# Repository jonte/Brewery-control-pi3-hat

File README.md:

This is a KiCad schematic of the outlines of a Raspberry Pi 2/3/4 HAT. The
schematic conforms to the official [HAT mechanical
specification](https://github.com/raspberrypi/hats/blob/master/hat-board-mechanical.pdf).

The intended use of this schematic is as a template when starting work on new
HATs.

Features:
* Empty board with the correct dimensions for a Pi HAT
* Cut-outs for camera and display ribbon cables
* 40-pin header in correct location

3D rendering:

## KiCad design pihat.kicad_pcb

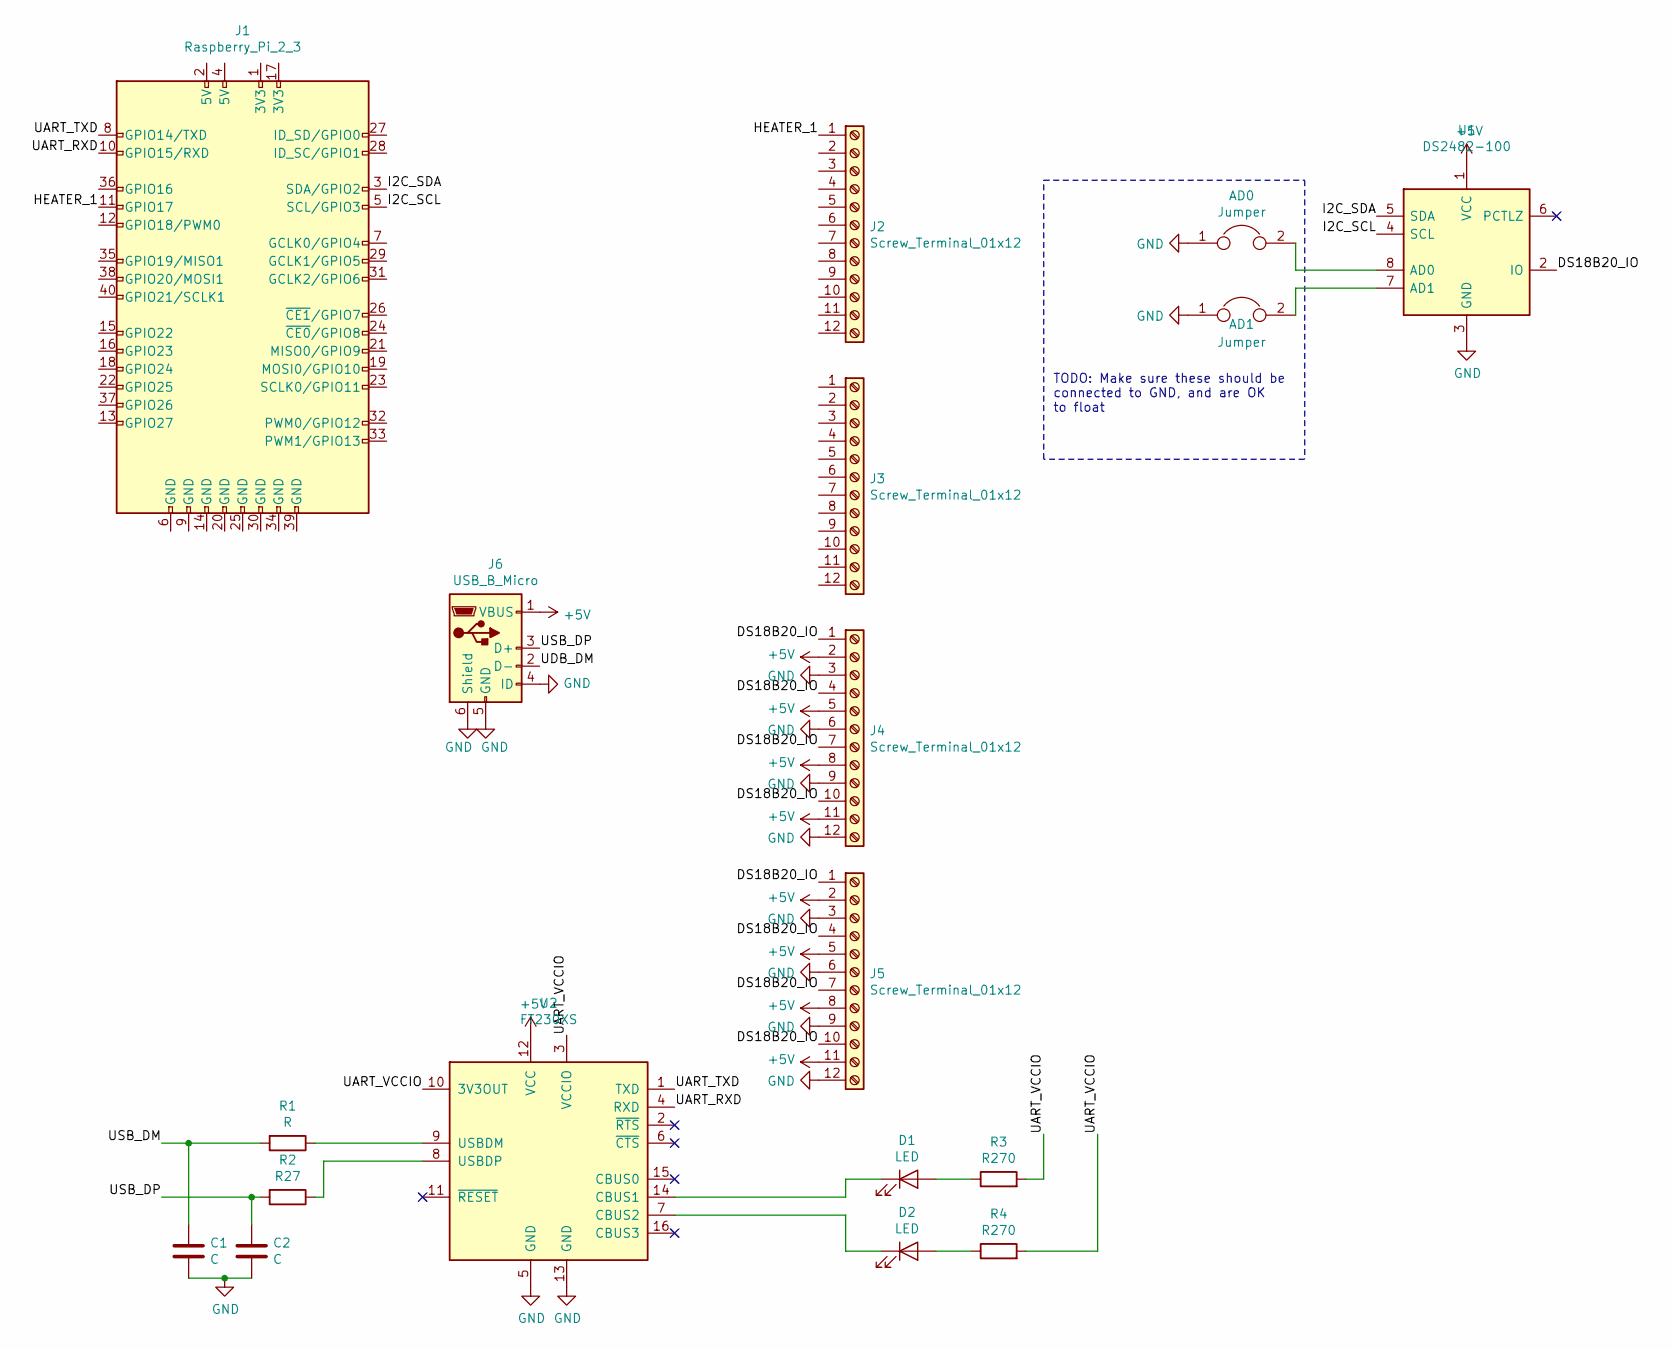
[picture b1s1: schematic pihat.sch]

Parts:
AD0, AD1: Jumper; PinHeader_1x02_P2.54mm_Vertical
C1, C2: C; C_0603_1608Metric_Pad1.05x0.95mm_HandSolder
D1, D2: LED; LED_0603_1608Metric_Pad1.05x0.95mm_HandSolder
J1: Raspberry_Pi_2_3; ESQ-120-14-T-D
J2, J3, J4, J5: Screw_Terminal_01x12; TerminalBlock_Phoenix_MPT-0,5-12-2.54_1x12_P2.54mm_Horizont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
J6: USB_B_Micro; USB_Micro-B_Wuerth_629105150521
R1: R; R_0603_1608Metric_Pad1.05x0.95mm_HandSolder
R2: R27; R_0603_1608Metric_Pad1.05x0.95mm_HandSolder
R3, R4: R270; R_0603_1608Metric_Pad1.05x0.95mm_HandSolder
U1: DS2482-100; SOIC-8_3.9x4.9mm_P1.27mm
U2: FT230XS; SSOP-16_3.9x4.9mm_P0.635mm

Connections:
+5V: J4.2, J4.5, J4.8, J4.11, J5.2, J5.5, J5.8, J5.11, J6.1 (VBUS), U1.1 (VCC), U2.12 (VCC)
/DS18B20_IO: J4.1, J4.4, J4.7, J4.10, J5.1, J5.4, J5.7, J5.10, U1.2 (IO)
/HEATER_1: J1.11 (GPIO17), J2.1
/I2C_SCL: J1.5 (SCL/GPIO3), U1.4 (SCL)
/I2C_SDA: J1.3 (SDA/GPIO2), U1.5 (SDA)
/UART_RXD: J1.10 (GPIO15/RXD), U2.4 (RXD)
/UART_TXD: J1.8 (GPIO14/TXD), U2.1 (TXD)
/UART_VCCIO: R3.2, R4.2, U2.3 (VCCIO), U2.10 (3V3OUT)
/UDB_DM: J6.2 (D-)
/USB_DM: C1.1, R1.2
/USB_DP: C2.1, J6.3 (D+), R2.2
GND: AD0.1, AD1.1, C1.2, C2.2, J4.3, J4.6, J4.9, J4.12, J5.3, J5.6, J5.9, J5.12, J6.4 (ID), J6.5 (GND), J6.6 (Shield), U1.3 (GND), U2.5 (GND), U2.13 (GND)
unnamed: AD0.2, U1.8 (AD0)
unnamed: AD1.2, U1.7 (AD1)
unnamed: D1.1 (K), U2.14 (CBUS1)
unnamed: D1.2 (A), R3.1
unnamed: D2.1 (K), U2.7 (CBUS2)
unnamed: D2.2 (A), R4.1
unnamed: R1.1, U2.9 (USBDM)
unnamed: R2.1, U2.8 (USBDP)

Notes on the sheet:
TODO: Make sure these should be connected to GND, and are OK to float

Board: 2 copper layers, 18 parts (9 on the bottom side), 19 nets, no tracks yet.

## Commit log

2019-10-14 Add 3d rendering to README
2019-10-14 Add template metadata
2020-01-21 Add initial schematic for hat
    This adds a USB<->UART converter and a 1-wire bus master, as well as
    screw connectors for heating elements and sensors.
